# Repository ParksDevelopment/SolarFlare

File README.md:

# SolarFlare
36 key keyboard for desktop use

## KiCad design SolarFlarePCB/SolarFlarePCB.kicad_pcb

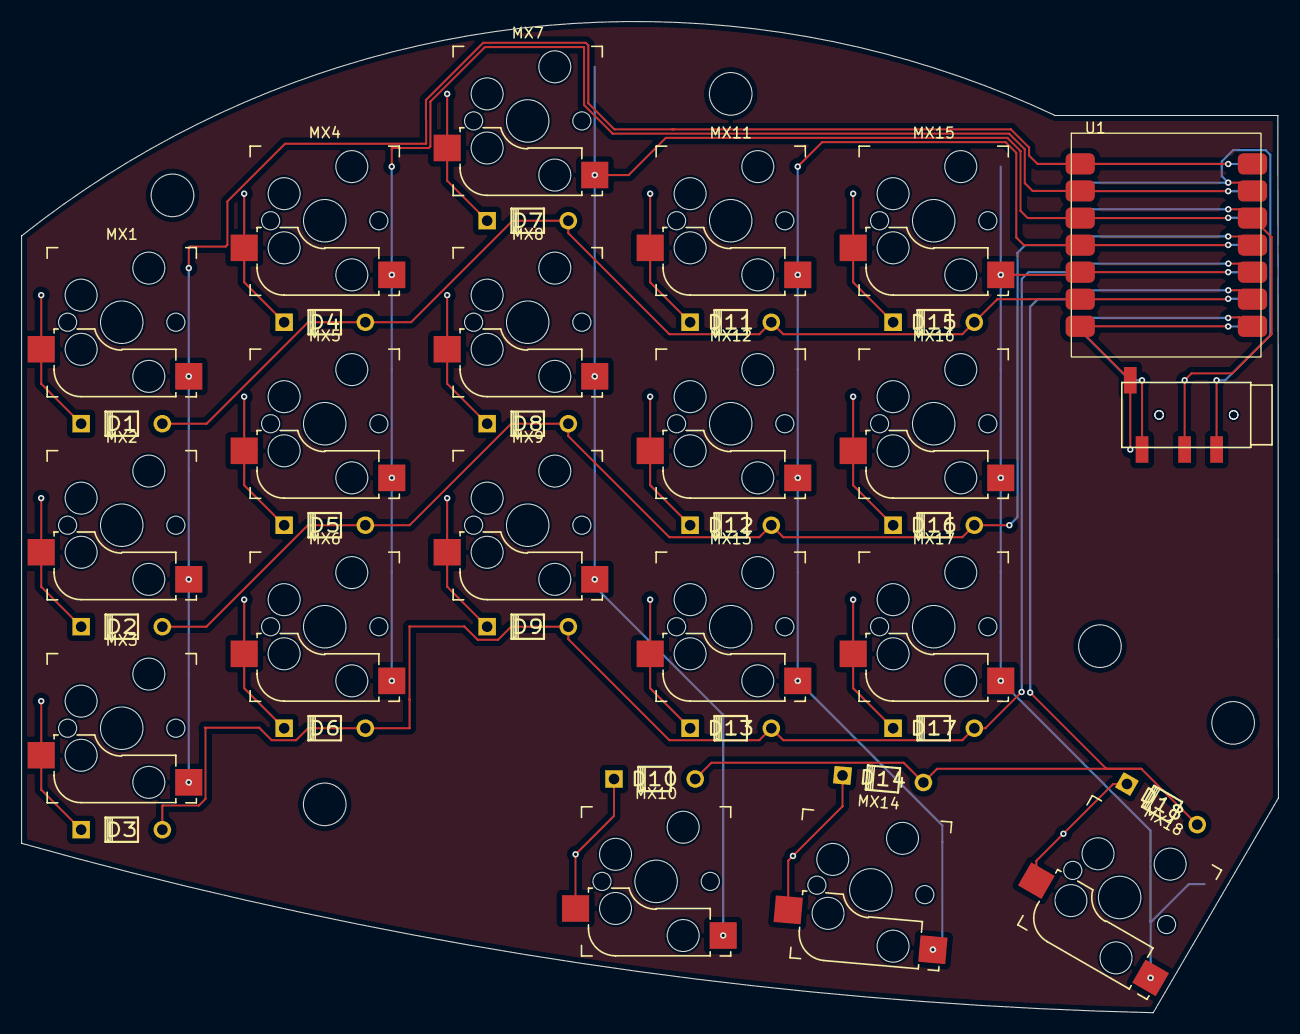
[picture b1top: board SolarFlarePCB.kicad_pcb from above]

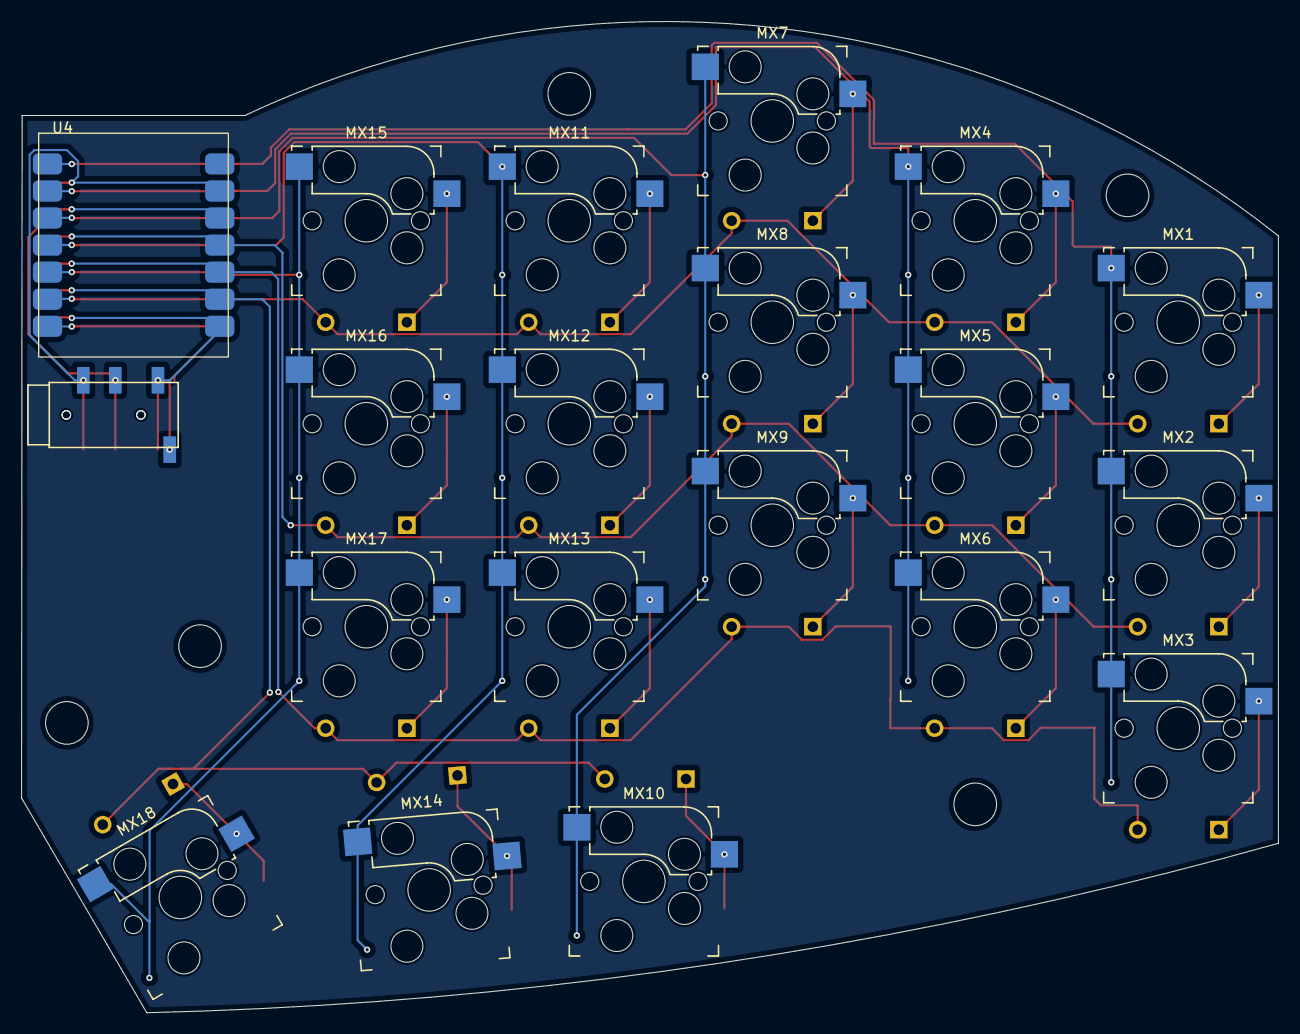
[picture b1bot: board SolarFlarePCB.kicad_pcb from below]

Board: 2 copper layers, 118.0 x 93.0 mm, 40 parts (2 on the bottom side), 31 nets.

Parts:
D1, D2, D3, D4, D5, D6, D7, D8, D9, D10, D11, D12, D13, D14, D15, D16, D17, D18: D_Small; Diode
MX1, MX2, MX3, MX4, MX5, MX6, MX7, MX8, MX9, MX10, MX11, MX12, MX13, MX14, MX15, MX16, MX17, MX18: MX-NoLED; Kailh_socket_MX_reversible
U1, U4: MOUDLE-SEEEDUINO-XIAO; MOUDLE14P-SMD-2.54-21X17.8MM
U2, U3: TRRS; TRRS-PJ-320D

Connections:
+3.3V: U1.12 (3V3), U2.3 (RING1), U3.3 (RING1), U4.12 (3V3)
/col0: MX15.1 (COL), MX16.1 (COL), MX17.1 (COL), MX18.1 (COL), U1.5 (PA8_A4_D4_SDA), U4.5 (PA8_A4_D4_SDA)
/col1: MX11.1 (COL), MX12.1 (COL), MX13.1 (COL), MX14.1 (COL), U1.4 (PA11_A3_D3), U4.4 (PA11_A3_D3)
/col2: MX7.1 (COL), MX8.1 (COL), MX9.1 (COL), MX10.1 (COL), U1.3 (PA10_A2_D2), U4.3 (PA10_A2_D2)
/col3: MX4.1 (COL), MX5.1 (COL), MX6.1 (COL), U1.2 (PA4_A1_D1), U4.2 (PA4_A1_D1)
/col4: MX1.1 (COL), MX2.1 (COL), MX3.1 (COL), U1.1 (PA02_A0_D0), U4.1 (PA02_A0_D0)
/row0: D1.1 (K), D4.1 (K), D7.1 (K), D11.1 (K), D15.1 (K), U1.6 (PA9_A5_D5_SCL), U4.6 (PA9_A5_D5_SCL)
/row1: D2.1 (K), D5.1 (K), D8.1 (K), D12.1 (K), D16.1 (K), U1.11 (PA6_A10_D10_MOSI), U4.11 (PA6_A10_D10_MOSI)
/row2: D3.1 (K), D6.1 (K), D9.1 (K), D13.1 (K), D17.1 (K), U1.10 (PA5_A9_D9_MISO), U4.10 (PA5_A9_D9_MISO)
/row3: D10.1 (K), D14.1 (K), D18.1 (K), U1.9 (PA7_A8_D8_SCK), U4.9 (PA7_A8_D8_SCK)
/rx: U1.8 (PB09_A7_D7_RX), U2.2 (TIP), U3.2 (TIP), U4.8 (PB09_A7_D7_RX)
/tx: U1.7 (PB08_A6_D6_TX), U2.1 (SLEEVE), U3.1 (SLEEVE), U4.7 (PB08_A6_D6_TX)
GND: U1.13 (GND), U2.4 (RING2), U3.4 (RING2), U4.13 (GND)
unnamed: D1.2 (A), MX1.2 (ROW)
unnamed: D2.2 (A), MX2.2 (ROW)
unnamed: D3.2 (A), MX3.2 (ROW)
unnamed: D4.2 (A), MX4.2 (ROW)
unnamed: D5.2 (A), MX5.2 (ROW)
unnamed: D6.2 (A), MX6.2 (ROW)
unnamed: D7.2 (A), MX7.2 (ROW)
unnamed: D8.2 (A), MX8.2 (ROW)
unnamed: D9.2 (A), MX9.2 (ROW)
unnamed: D10.2 (A), MX10.2 (ROW)
unnamed: D11.2 (A), MX11.2 (ROW)
unnamed: D12.2 (A), MX12.2 (ROW)
unnamed: D13.2 (A), MX13.2 (ROW)
unnamed: D14.2 (A), MX14.2 (ROW)
unnamed: D15.2 (A), MX15.2 (ROW)
unnamed: D16.2 (A), MX16.2 (ROW)
unnamed: D17.2 (A), MX17.2 (ROW)
unnamed: D18.2 (A), MX18.2 (ROW)

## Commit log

2024-11-12 PCB Init
2024-11-13 starting to model
2024-11-21 Final push for production
